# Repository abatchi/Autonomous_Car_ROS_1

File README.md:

# Autonomous Systems Project Team 08

# 🚀 Milestone 2

## 📌 Overview
Milestone 2 focuses on enhancements in software, simulation, and Hardware testing of the vehicle and motors. This phase includes crucial improvements in **Teleop**, **OLR (Open Loop Response)**, and system integration.

## 📁 Project Structure
The following key components are included in this milestone:

- **`python_scripts/`**: Contains essential scripts for teleoperation and OLR.
- **`launch/`**: Houses the necessary launch files for initializing the system.
- **Additional components**: Any supplementary configurations, ROS packages, or dependencies required for smooth operation.

# 📜 Milestone 1 Deliverables
For reference, the deliverables from Milestone 1 can be found in the following directories:

- **Hardware Deliverables:** Located in  
  📂 `Autonomous_Systems_Project_Team_08/Milestone1/Hardware_Milestone_01_Team_08/`
- **Simulation Deliverables:** Located in  
  📂 `Autonomous_Systems_Project_Team_08/Milestone1/Simulation_Milestone_01_Team_08/`

These directories contain all the necessary resources, including **hardware setup instructions for the Raspberry Pi 4B** and **simulation-based deliverables** from the first milestone.

## 📌 Next Steps
- Fine-tune the teleoperation and OLR functionalities.
- Validate performance through both **simulation** and **real-world testing**.
- Prepare documentation and further refinements for the next milestone.

---
📌 *This project is part of the Autonomous Systems course, developed by Team 08.* 🚀

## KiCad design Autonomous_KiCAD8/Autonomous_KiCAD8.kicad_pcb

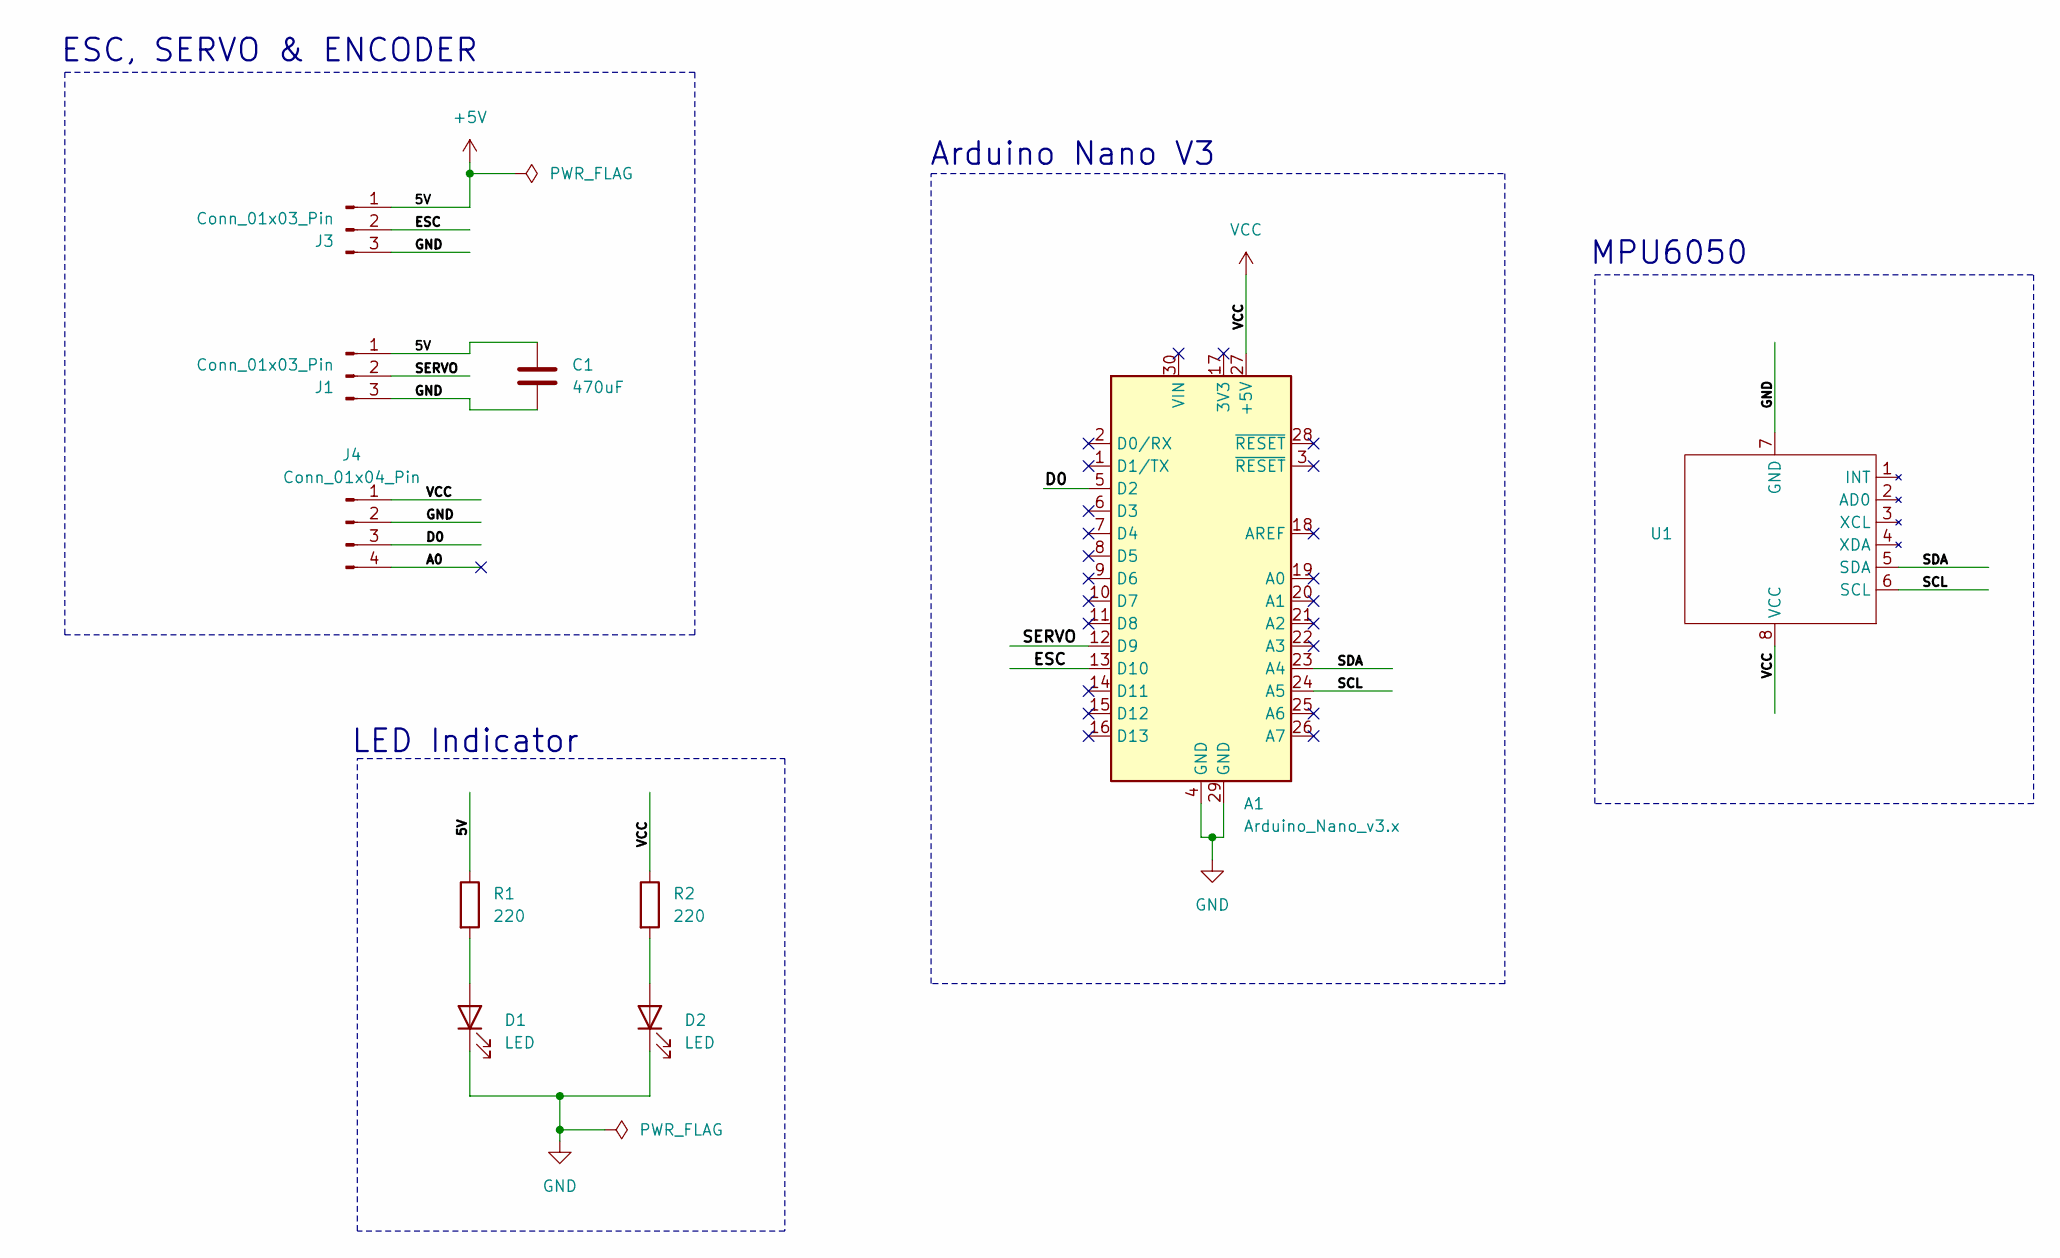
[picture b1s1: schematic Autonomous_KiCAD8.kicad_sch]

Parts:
A1: Arduino_Nano_v3.x; Arduino_Nano
C1: 470uF; CP_Radial_D4.0mm_P2.00mm
D1, D2: LED; LED_D5.0mm
J1, J3: Conn_01x03_Pin; PinHeader_1x03_P2.54mm_Vertical
J4: Conn_01x04_Pin; PinHeader_1x04_P2.54mm_Vertical
R1, R2: 220; R_Axial_DIN0207_L6.3mm_D2.5mm_P2.54mm_Vertical
U1: MPU6050

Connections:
+5V: C1.1, J1.1, J3.1, R1.1
/A0: J4.4
/D0: A1.5 (D2), J4.3
/ESC: A1.13 (D10), J3.2
/SCL: A1.24 (A5), U1.6 (SCL)
/SDA: A1.23 (A4), U1.5 (SDA)
/SERVO: A1.12 (D9), J1.2
GND: A1.4 (GND), A1.29 (GND), C1.2, D1.1 (K), D2.1 (K), J1.3, J3.3, J4.2, U1.7 (GND)
unnamed: D1.2 (A), R1.2
unnamed: D2.2 (A), R2.2
VCC: A1.27 (+5V), J4.1, R2.1, U1.8 (VCC)

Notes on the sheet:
LED Indicator
Arduino Nano V3
MPU6050
ESC, SERVO & ENCODER

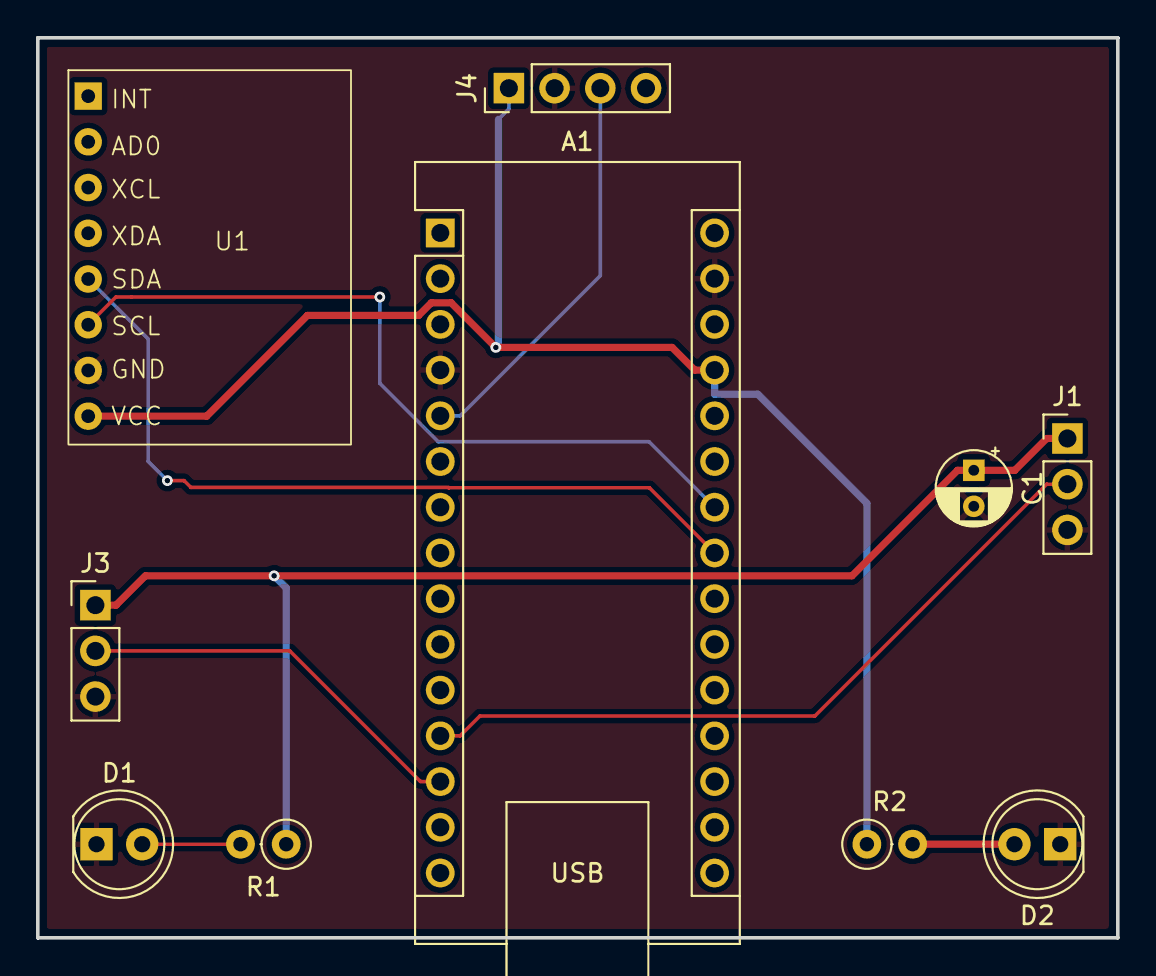
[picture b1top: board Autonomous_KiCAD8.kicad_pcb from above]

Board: 2 copper layers, 60.0 x 50.0 mm, 10 parts (0 on the bottom side), 10 nets.

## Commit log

2025-02-22 Add files via upload
    contains the required screenshots from the terminal
2025-02-22 Added my_new-folder
2025-02-22 Renamed my_new_folder to Milestone1
2025-02-22 Add files via upload
    the two required screenshots from the terminal are in the zip file
2025-02-22 Added Simulation_Milestone_01_Team_08 and Hardware_Milestone_01_Team_08
2025-02-22 Added Hardware & Simulation
2025-02-22 Add files via upload
    The file contains the requested screenshots from the raspberry pi terminal
2025-02-22 Copied ROS package to Simulation_Milestone_01_Team_08
2025-02-25 Create Hardware_Package_Team_8
2025-02-25 Done
2025-03-10 Added Milestone_02_Team_08 folder with .gitkeep
2025-03-10 Added python_scripts folder inside Milestone_02_Team_08
2025-03-10 Added OLR and Teleop files to python_scripts
2025-03-11 Added launch folder & the launch file Autonomous_Systems_MS_2_Team_08.launch inside Milestone_02_Team_08
2025-03-11 Added .gitkeep to track autonomous_system_project_team_08 folder
2025-03-11 Added package files and ensured tracking of src and launch folders
2025-03-11 Add files via upload
    Added package files and ensured tracking of src and launch folders
2025-03-11 Updated the Teleop code
2025-03-11 Add files via upload
    Added a screenshot for the printed results of the OLR node showing the rqt_graphs
    Added a screenshot for the printed results of the Teleop node showing the rqt_graphs
2025-03-11 Add files via upload
    A recorded video for OLR node
2025-03-12 Added Arduino_code folder with .gitkeep
2025-03-12 Added BLDC_SERVO_CONTROL file in Arduino_code
2025-03-12 Updated BLDC_SERVO_CONTROL in Arduino_code
2025-04-13 Added The Speed & Lateral Control Nodes
2025-04-14 Added MS3 launch file
2025-04-14 Added Hardware RaspberryPi Nodes
2025-04-14 Added Controller RaspberryPi Nodes
2025-04-14 Added Arduino Folder
2025-04-16 Added Arduino code
2025-04-16 Added Autonomous PCB
2025-04-16 Added ROS control Video
2025-04-27 Added Milestone 4
2025-04-27 Update Milestone 1
2025-04-30 Create LICENSE
2025-05-02 Added Simulation Video
2025-05-10 Added Milestone 5 Simulation files
2025-05-10 Added Simulation MS_05 Folder
2025-05-17 Added Hardware ROS Package
2025-05-18 Added Case 1 Hardware
2025-05-18 Added Autonomous final Report
2025-05-18 Added Hardware Obstacle Avoidance Task
2025-05-22 Added Noisy/Filtered data graphs
2025-06-07 Add new folder: Arduino_Code
